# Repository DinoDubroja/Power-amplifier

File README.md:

# Power-amplifier
A general purpose power amplifier for lab use.

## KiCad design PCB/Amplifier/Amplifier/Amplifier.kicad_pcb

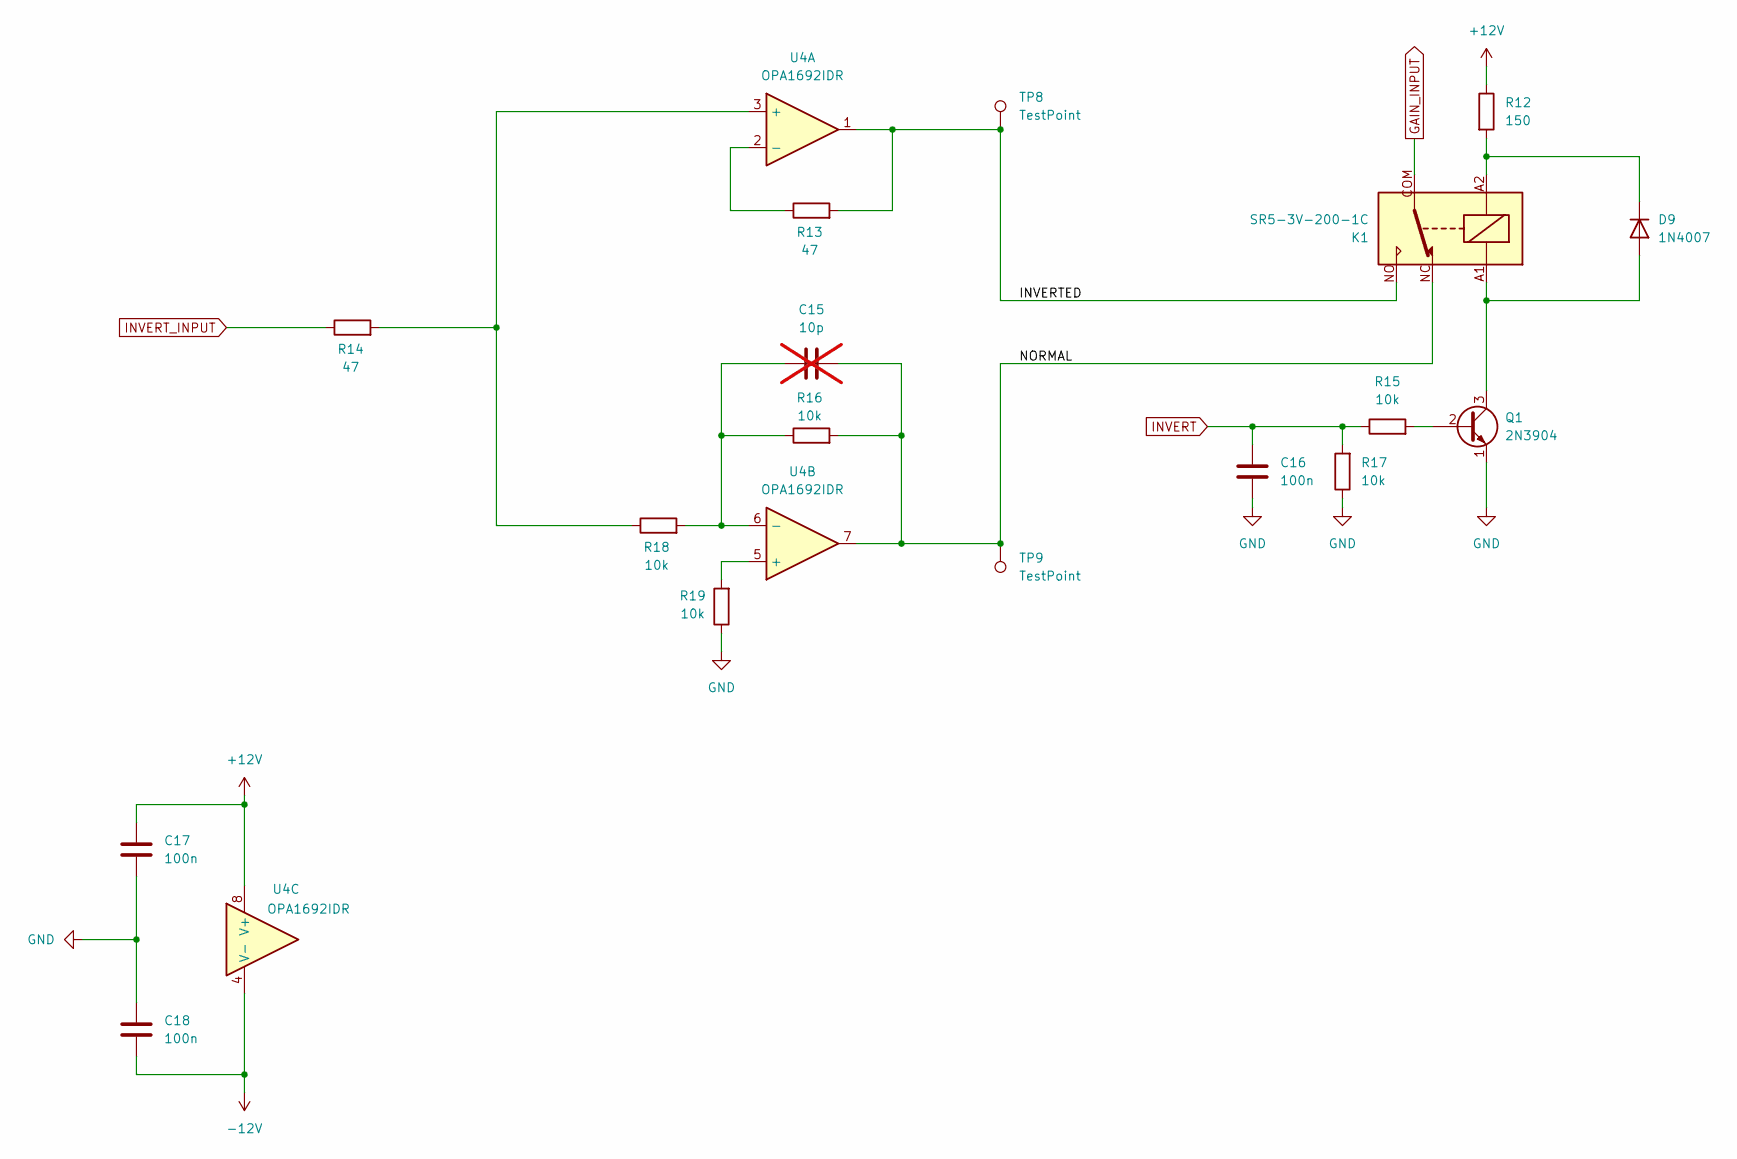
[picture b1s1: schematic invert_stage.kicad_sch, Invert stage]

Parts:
C15: 10p; C_Disc_D4.3mm_W1.9mm_P5.00mm; not fitted
C16, C17, C18: 100n; C_Disc_D4.3mm_W1.9mm_P5.00mm
D9: 1N4007; D_DO-15_P10.16mm_Horizontal
K1: SR5-3V-200-1C; SR53V2001C; Manufacturer_Part_Number SR5-3V-200-1C; Mouser Part Number 179-SR5-3V-200-1C
Q1: 2N3904; TO-92_Inline
R12: 150; R_Axial_DIN0207_L6.3mm_D2.5mm_P10.16mm_Horizontal
R13, R14: 47; R_Axial_DIN0207_L6.3mm_D2.5mm_P10.16mm_Horizontal
R15, R16, R17, R18, R19: 10k; R_Axial_DIN0207_L6.3mm_D2.5mm_P10.16mm_Horizontal
TP8, TP9: TestPoint; Pin_D1.2mm_L11.3mm_W3.0mm_Flat
U4: OPA1692IDR; SOIC127P600X175-8N; Manufacturer_Part_Number OPA1692IDR; Mouser Part Number 595-OPA1692IDR

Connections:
+12V: C17.1, R12.1, U4.8 (V+); also elsewhere on the board
-12V: C18.2, U4.4 (V-); also elsewhere on the board
/Invert stage/INVERTED: K1.NO, R13.2, TP8.1, U4.1
/Invert stage/NORMAL: C15.2, K1.NC, R16.2, TP9.1, U4.7
GAIN_INPUT: K1.COM; also elsewhere on the board
GND: C16.2, C17.2, C18.1, Q1.1 (E), R17.1, R19.1; also elsewhere on the board
INVERT: C16.1, R15.1, R17.2; also elsewhere on the board
INVERT_INPUT: R14.1; also elsewhere on the board
unnamed: D9.2 (A), K1.A1, Q1.3 (C)
unnamed: D9.1 (K), K1.A2, R12.2
unnamed: Q1.2 (B), R15.2
unnamed: R14.2, R18.1, U4.3 (+)
unnamed: R13.1, U4.2 (-)
unnamed: R19.2, U4.5 (+)
unnamed: C15.1, R16.1, R18.2, U4.6 (-)

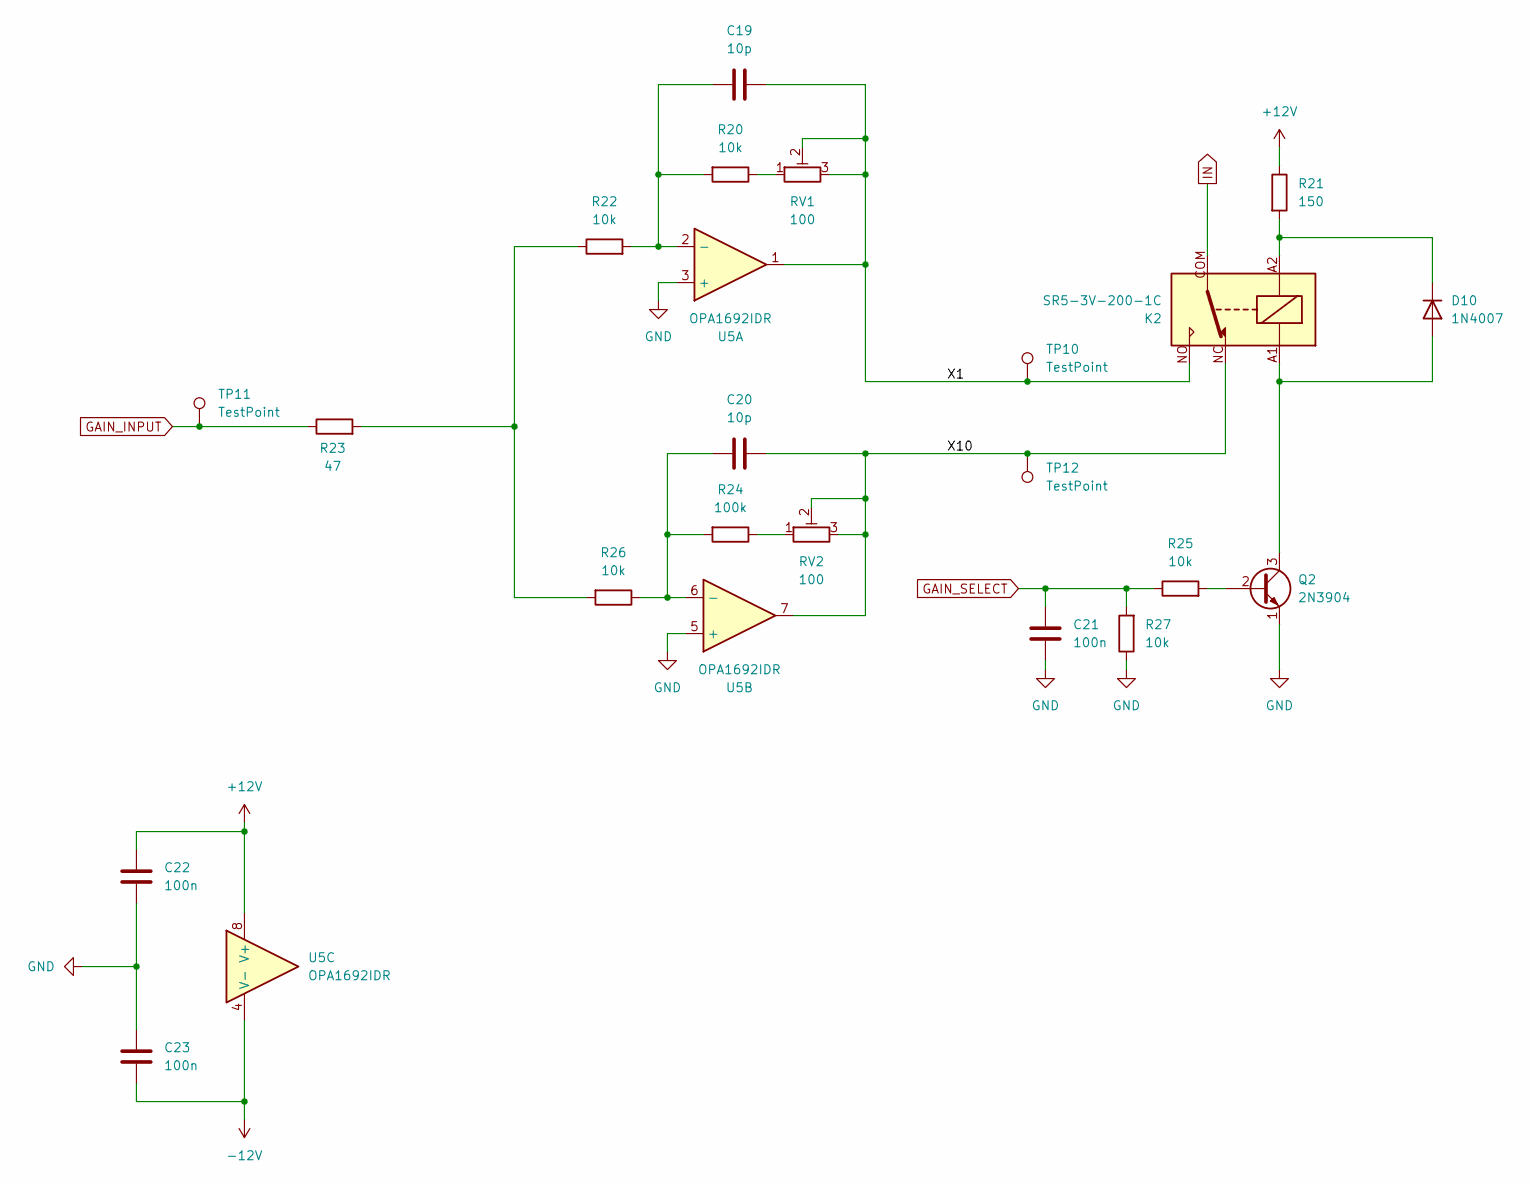
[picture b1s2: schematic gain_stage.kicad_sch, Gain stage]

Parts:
C19, C20: 10p; C_Disc_D4.3mm_W1.9mm_P5.00mm
C21, C22, C23: 100n; C_Disc_D4.3mm_W1.9mm_P5.00mm
D10: 1N4007; D_DO-15_P10.16mm_Horizontal
K2: SR5-3V-200-1C; SR53V2001C; Manufacturer_Part_Number SR5-3V-200-1C; Mouser Part Number 179-SR5-3V-200-1C
Q2: 2N3904; TO-92_Inline
R20, R22, R25, R26, R27: 10k; R_Axial_DIN0207_L6.3mm_D2.5mm_P10.16mm_Horizontal
R21: 150; R_Axial_DIN0207_L6.3mm_D2.5mm_P10.16mm_Horizontal
R23: 47; R_Axial_DIN0207_L6.3mm_D2.5mm_P10.16mm_Horizontal
R24: 100k; R_Axial_DIN0207_L6.3mm_D2.5mm_P10.16mm_Horizontal
RV1, RV2: 100; Potentiometer_Bourns_3296W_Vertical
TP10, TP11, TP12: TestPoint; Pin_D1.2mm_L11.3mm_W3.0mm_Flat
U5: OPA1692IDR; SOIC127P600X175-8N; Manufacturer_Part_Number OPA1692IDR; Mouser Part Number 595-OPA1692IDR

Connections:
+12V: C22.1, R21.1, U5.8 (V+); also elsewhere on the board
-12V: C23.2, U5.4 (V-); also elsewhere on the board
/Gain stage/X1: C19.2, K2.NO, RV1.2, RV1.3, TP10.1, U5.1
/Gain stage/X10: C20.2, K2.NC, RV2.2, RV2.3, TP12.1, U5.7
GAIN_INPUT: R23.1, TP11.1; also elsewhere on the board
GAIN_SELECT: C21.1, R25.1, R27.2; also elsewhere on the board
GND: C21.2, C22.2, C23.1, Q2.1 (E), R27.1, U5.3 (+), U5.5 (+); also elsewhere on the board
IN: K2.COM; also elsewhere on the board
unnamed: D10.2 (A), K2.A1, Q2.3 (C)
unnamed: D10.1 (K), K2.A2, R21.2
unnamed: Q2.2 (B), R25.2
unnamed: R20.1, RV1.1
unnamed: R22.1, R23.2, R26.2
unnamed: R24.1, RV2.1
unnamed: C19.1, R20.2, R22.2, U5.2 (-)
unnamed: C20.1, R24.2, R26.1, U5.6 (-)

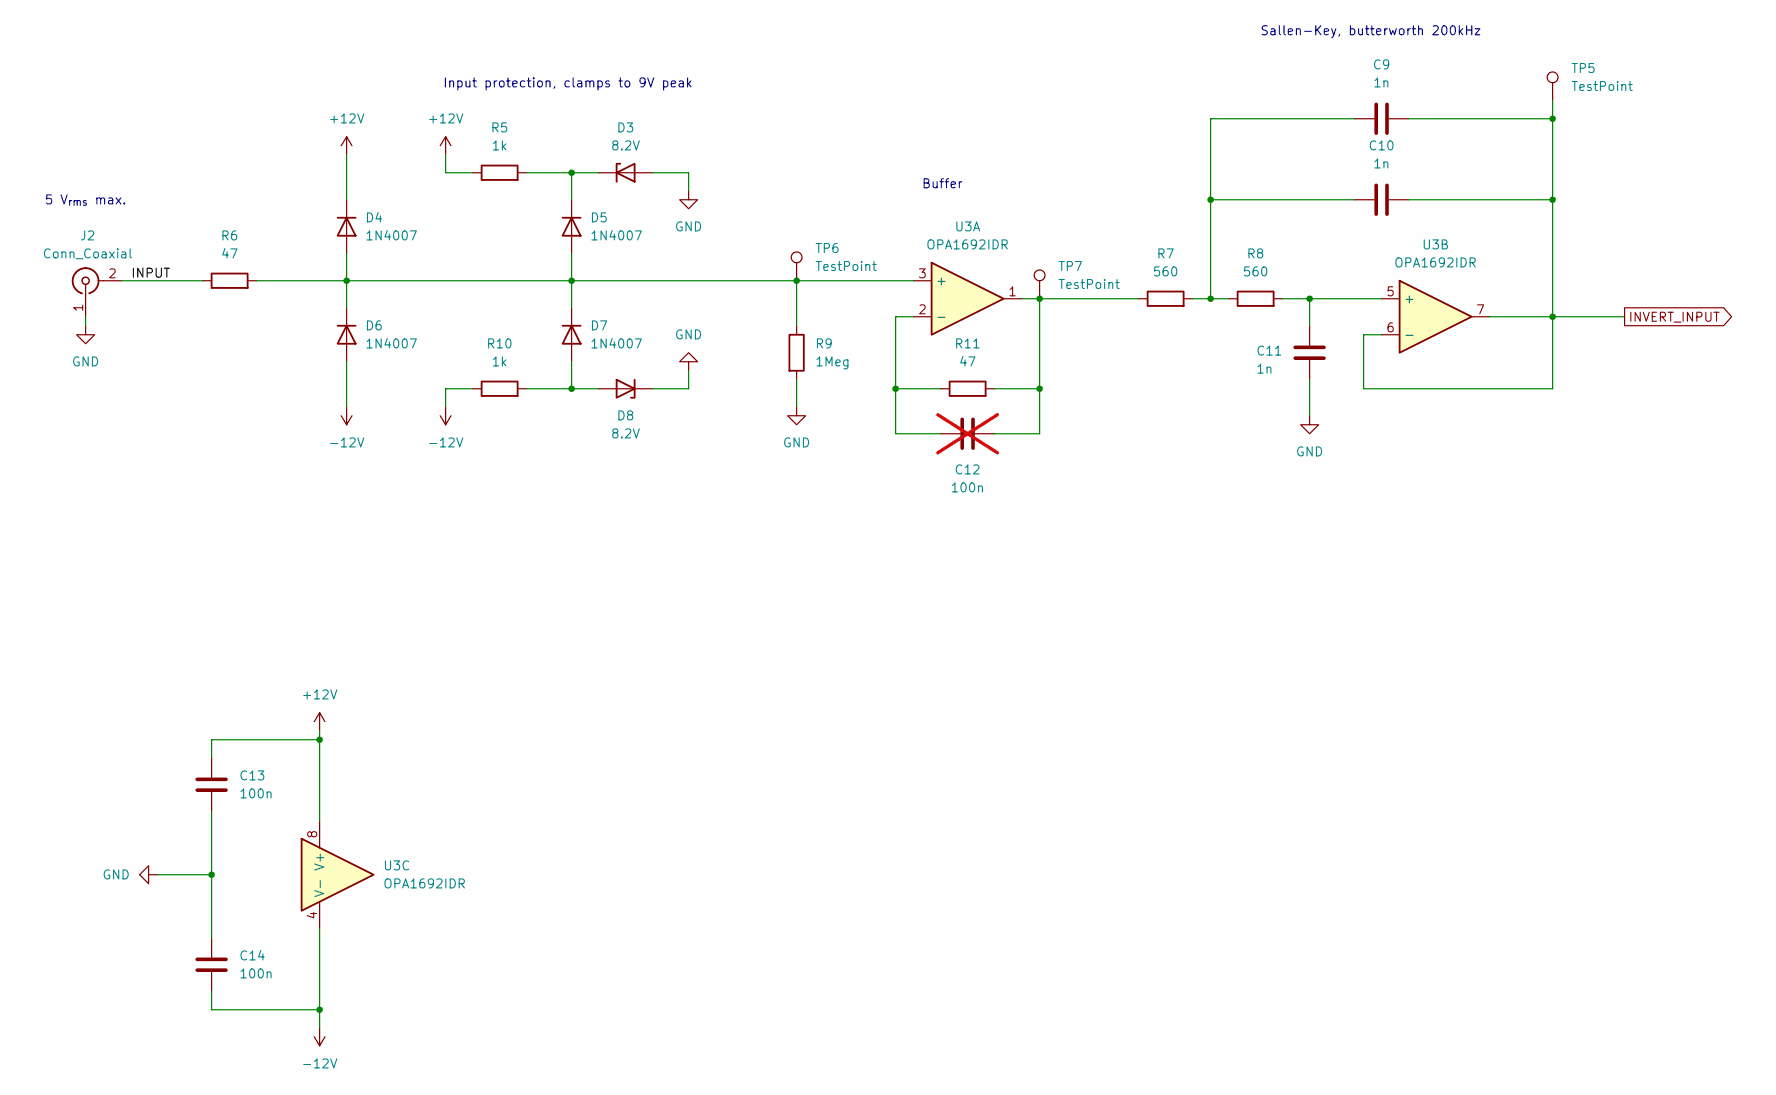
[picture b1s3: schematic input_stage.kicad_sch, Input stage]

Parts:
C9, C10, C11: 1n; C_Rect_L7.2mm_W2.5mm_P5.00mm_FKS2_FKP2_MKS2_MKP2
C12: 100n; C_Disc_D4.3mm_W1.9mm_P5.00mm; not fitted
C13, C14: 100n; C_Disc_D4.3mm_W1.9mm_P5.00mm
D3, D8: 8.2V; D_DO-35_SOD27_P10.16mm_Horizontal
D4, D5, D6, D7: 1N4007; D_DO-15_P10.16mm_Horizontal
J2: Conn_Coaxial; 52220061
R5, R10: 1k; R_Axial_DIN0207_L6.3mm_D2.5mm_P10.16mm_Horizontal
R6, R11: 47; R_Axial_DIN0207_L6.3mm_D2.5mm_P10.16mm_Horizontal
R7, R8: 560; R_Axial_DIN0207_L6.3mm_D2.5mm_P10.16mm_Horizontal
R9: 1Meg; R_Axial_DIN0207_L6.3mm_D2.5mm_P10.16mm_Horizontal
TP5, TP6, TP7: TestPoint; Pin_D1.2mm_L11.3mm_W3.0mm_Flat
U3: OPA1692IDR; SOIC127P600X175-8N; Manufacturer_Part_Number OPA1692IDR; Mouser Part Number 595-OPA1692IDR

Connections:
+12V: C13.1, D4.1 (K), R5.1, U3.8 (V+); also elsewhere on the board
-12V: C14.2, D6.2 (A), R10.1, U3.4 (V-); also elsewhere on the board
/Input stage/INPUT: J2.2 (Ext), R6.1
GND: C11.2, C13.2, C14.1, D3.2 (A), D8.1 (K), J2.1 (In), R9.2; also elsewhere on the board
INVERT_INPUT: C9.2, C10.2, TP5.1, U3.6 (-), U3.7; also elsewhere on the board
unnamed: C9.1, C10.1, R7.2, R8.1
unnamed: C12.2, R7.1, R11.2, TP7.1, U3.1
unnamed: D3.1 (K), D5.1 (K), R5.2
unnamed: D4.2 (A), D5.2 (A), D6.1 (K), D7.1 (K), R6.2, R9.1, TP6.1, U3.3 (+)
unnamed: D7.2 (A), D8.2 (A), R10.2
unnamed: C12.1, R11.1, U3.2 (-)
unnamed: C11.1, R8.2, U3.5 (+)

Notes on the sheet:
Input protection, clamps to 9V peak
5 V_{rms} max.
Buffer
Sallen-Key, butterworth 200kHz

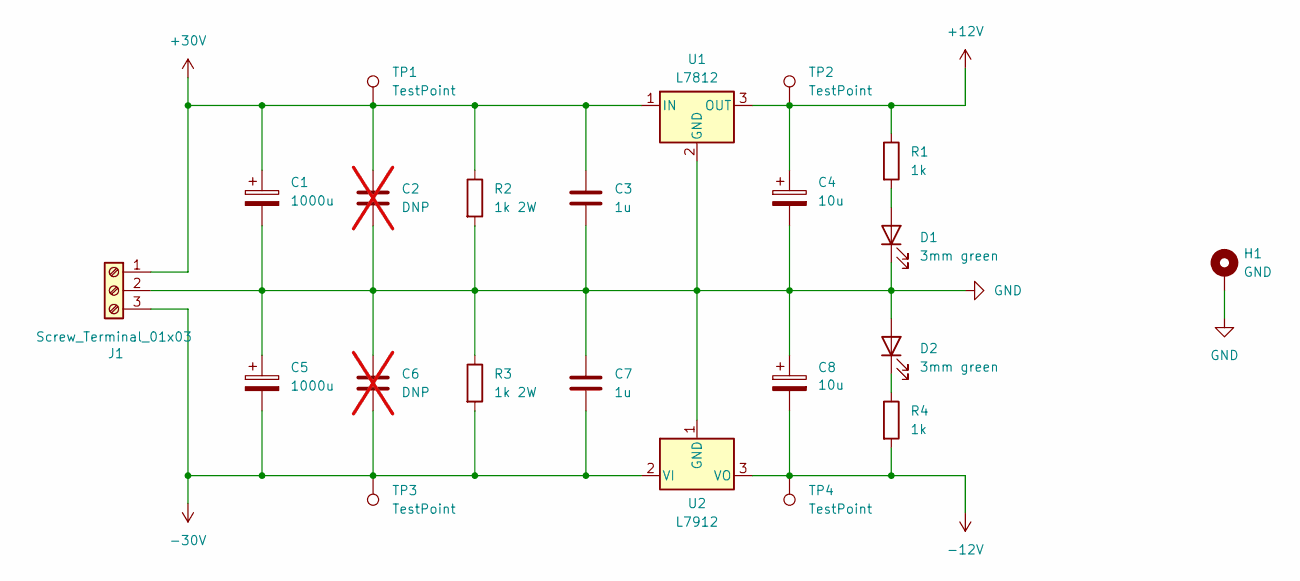
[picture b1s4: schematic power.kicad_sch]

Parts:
C1, C5: 1000u; CP_Radial_D16.0mm_P7.50mm
C2, C6: DNP; C_Disc_D4.3mm_W1.9mm_P5.00mm; not fitted
C3, C7: 1u; C_Rect_L7.2mm_W4.5mm_P5.00mm_FKS2_FKP2_MKS2_MKP2
C4, C8: 10u; CP_Radial_D4.0mm_P2.00mm
D1, D2: 3mm green; LED_D3.0mm
H1: GND; MountingHole_4.3mm_M4_Pad
J1: Screw_Terminal_01x03; TerminalBlock_Phoenix_MKDS-1,5-3_1x03_P5.00mm_Horizontal
R1, R4: 1k; R_Axial_DIN0207_L6.3mm_D2.5mm_P10.16mm_Horizontal
R2, R3: 1k 2W; R_Axial_DIN0411_L9.9mm_D3.6mm_P15.24mm_Horizontal
TP1, TP2, TP3, TP4: TestPoint; Pin_D1.2mm_L11.3mm_W3.0mm_Flat
U1: L7812; TO-220-3_Vertical
U2: L7912; TO-220-3_Vertical

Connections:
+12V: C4.1, R1.1, TP2.1, U1.3 (OUT); also elsewhere on the board
+30V: C1.1, C2.1, C3.1, J1.1, R2.1, TP1.1, U1.1 (IN); also elsewhere on the board
-12V: C8.2, R4.2, TP4.1, U2.3 (VO); also elsewhere on the board
-30V: C5.2, C6.2, C7.2, J1.3, R3.2, TP3.1, U2.2 (VI); also elsewhere on the board
GND: C1.2, C2.2, C3.2, C4.2, C5.1, C6.1, C7.1, C8.1, D1.1 (K), D2.2 (A), H1.1, J1.2, R2.2, R3.1, U1.2 (GND), U2.1 (GND); also elsewhere on the board
unnamed: D1.2 (A), R1.2
unnamed: D2.1 (K), R4.1

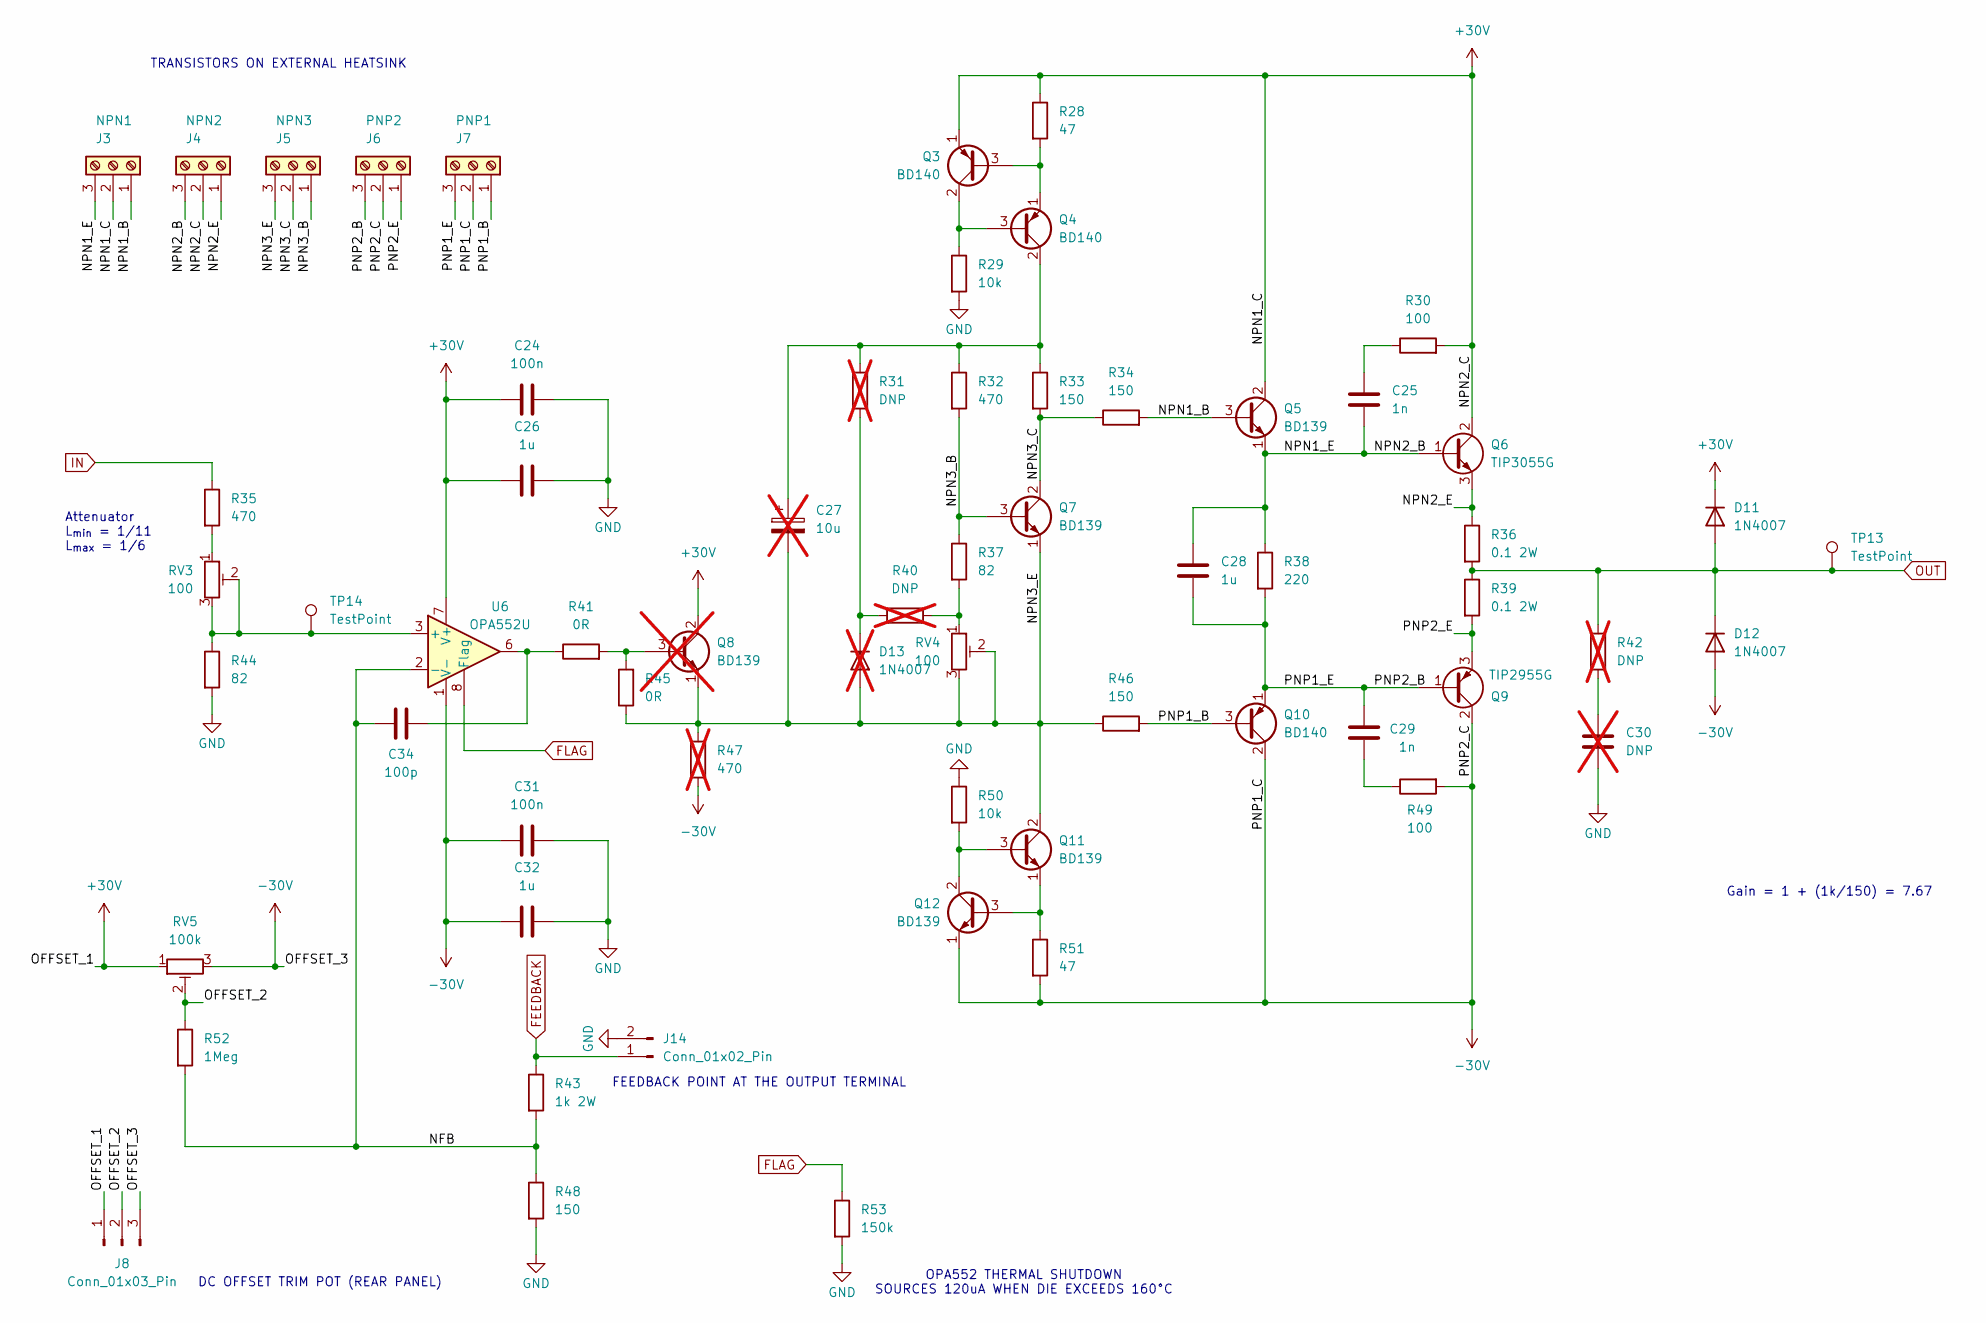
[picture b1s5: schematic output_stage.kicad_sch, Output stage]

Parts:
C24, C31: 100n; C_Disc_D4.3mm_W1.9mm_P5.00mm
C25, C29: 1n; C_Rect_L7.2mm_W2.5mm_P5.00mm_FKS2_FKP2_MKS2_MKP2
C26, C28, C32: 1u; C_Rect_L7.2mm_W4.5mm_P5.00mm_FKS2_FKP2_MKS2_MKP2
C27: 10u; CP_Radial_D4.0mm_P2.00mm; not fitted
C30: DNP; C_Disc_D4.3mm_W1.9mm_P5.00mm; not fitted
C34: 100p; C_Disc_D4.3mm_W1.9mm_P5.00mm
D11, D12: 1N4007; D_DO-15_P10.16mm_Horizontal
D13: 1N4007; D_DO-15_P10.16mm_Horizontal; not fitted
J3: NPN1; TerminalBlock_Phoenix_MKDS-1,5-3_1x03_P5.00mm_Horizontal
J4: NPN2; TerminalBlock_Phoenix_MKDS-1,5-3_1x03_P5.00mm_Horizontal
J5: NPN3; TerminalBlock_Phoenix_MKDS-1,5-3_1x03_P5.00mm_Horizontal
J6: PNP2; TerminalBlock_Phoenix_MKDS-1,5-3_1x03_P5.00mm_Horizontal
J7: PNP1; TerminalBlock_Phoenix_MKDS-1,5-3_1x03_P5.00mm_Horizontal
J8: Conn_01x03_Pin; JST_XH_B3B-XH-A_1x03_P2.50mm_Vertical
J14: Conn_01x02_Pin; JST_XH_B2B-XH-A_1x02_P2.50mm_Vertical
Q3, Q4: BD140; TO-126-3_Vertical
Q5, Q7: BD139; TerminalBlock_Phoenix_MKDS-1,5-3_1x03_P5.00mm_Horizontal
Q6: TIP3055G; TerminalBlock_Phoenix_MKDS-1,5-3_1x03_P5.00mm_Horizontal
Q8: BD139; TO-126-3_Vertical; not fitted
Q9: TIP2955G; TerminalBlock_Phoenix_MKDS-1,5-3_1x03_P5.00mm_Horizontal
Q10: BD140; TerminalBlock_Phoenix_MKDS-1,5-3_1x03_P5.00mm_Horizontal
Q11, Q12: BD139; TO-126-3_Vertical
R28, R51: 47; R_Axial_DIN0207_L6.3mm_D2.5mm_P10.16mm_Horizontal
R29, R50: 10k; R_Axial_DIN0207_L6.3mm_D2.5mm_P10.16mm_Horizontal
R30, R49: 100; R_Axial_DIN0207_L6.3mm_D2.5mm_P10.16mm_Horizontal
R31, R40, R42: DNP; R_Axial_DIN0207_L6.3mm_D2.5mm_P10.16mm_Horizontal; not fitted
R32, R35: 470; R_Axial_DIN0207_L6.3mm_D2.5mm_P10.16mm_Horizontal
R33, R34, R46, R48: 150; R_Axial_DIN0207_L6.3mm_D2.5mm_P10.16mm_Horizontal
R36, R39: 0.1 2W; R_Axial_DIN0516_L15.5mm_D5.0mm_P20.32mm_Horizontal
R37, R44: 82; R_Axial_DIN0207_L6.3mm_D2.5mm_P10.16mm_Horizontal
R38: 220; R_Axial_DIN0207_L6.3mm_D2.5mm_P10.16mm_Horizontal
R41, R45: 0R; R_Axial_DIN0207_L6.3mm_D2.5mm_P10.16mm_Horizontal
R43: 1k 2W; R_Axial_DIN0411_L9.9mm_D3.6mm_P15.24mm_Horizontal
R47: 470; R_Axial_DIN0207_L6.3mm_D2.5mm_P10.16mm_Horizontal; not fitted
R52: 1Meg; R_Axial_DIN0207_L6.3mm_D2.5mm_P10.16mm_Horizontal
R53: 150k; R_Axial_DIN0207_L6.3mm_D2.5mm_P10.16mm_Horizontal
RV3, RV4: 100; Potentiometer_Bourns_3296W_Vertical
RV5: 100k
TP13, TP14: TestPoint; Pin_D1.2mm_L11.3mm_W3.0mm_Flat
U6: OPA552U; SOIC-8_3.9x4.9mm_P1.27mm

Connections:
+30V: C24.1, C26.1, D11.1 (K), J3.2, J4.2, J8.1, Q3.1 (E), Q5.2 (C), Q6.2 (C), Q8.2 (C), R28.1, R30.2, RV5.1, U6.7 (V+); also elsewhere on the board
-30V: C31.1, C32.1, D12.2 (A), J6.2, J7.2, J8.3, Q9.2 (C), Q10.2 (C), Q12.1 (E), R47.1, R49.2, R51.2, RV5.3, U6.1 (V-), U6.4 (V-), U6.5 (V-); also elsewhere on the board
/Output stage/NFB: C34.1, R43.2, R48.1, R52.2, U6.2 (-)
/Output stage/NPN1_B: J3.1, Q5.3 (B), R34.2
/Output stage/NPN1_E: C25.2, C28.1, J3.3, J4.3, Q5.1 (E), Q6.1 (B), R38.1
/Output stage/NPN2_E: J4.1, Q6.3 (E), R36.1
/Output stage/NPN3_B: J5.1, Q7.3 (B), R32.2, R37.1
/Output stage/NPN3_C: J5.2, Q7.2 (C), R33.2, R34.1
/Output stage/NPN3_E: C27.2, D13.2 (A), J5.3, Q7.1 (E), Q8.1 (E), Q11.2 (C), R45.1, R46.1, R47.2, RV4.2, RV4.3
/Output stage/OFFSET_2: J8.2, R52.1, RV5.2
/Output stage/PNP1_B: J7.1, Q10.3 (B), R46.2
/Output stage/PNP1_E: C28.2, C29.2, J6.3, J7.3, Q9.1 (B), Q10.1 (E), R38.2
/Output stage/PNP2_E: J6.1, Q9.3 (E), R39.2
FEEDBACK: J14.1, R43.1
FLAG: R53.1, U6.8 (Flag); also elsewhere on the board
GND: C24.2, C26.2, C30.2, C31.2, C32.2, J14.2, R29.2, R44.2, R48.2, R50.1, R53.2; also elsewhere on the board
IN: R35.1; also elsewhere on the board
unnamed: C25.1, R30.1
unnamed: C29.1, R49.1
unnamed: C30.1, R42.2
unnamed: C34.2, R41.1, U6.6
unnamed: D13.1 (K), R31.1, R40.2
unnamed: Q3.3 (B), Q4.1 (E), R28.2
unnamed: Q3.2 (C), Q4.3 (B), R29.1
unnamed: C27.1, Q4.2 (C), R31.2, R32.1, R33.1
unnamed: Q8.3 (B), R41.2, R45.2
unnamed: Q11.3 (B), Q12.2 (C), R50.2
unnamed: Q11.1 (E), Q12.3 (B), R51.1
unnamed: R35.2, RV3.1
unnamed: R37.2, R40.1, RV4.1
unnamed: R44.1, RV3.2, RV3.3, TP14.1, U6.3 (+)
OUT: D11.2 (A), D12.1 (K), R36.2, R39.1, R42.1, TP13.1; also elsewhere on the board

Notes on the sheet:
FEEDBACK POINT AT THE OUTPUT TERMINAL
OPA552 THERMAL SHUTDOWN SOURCES 120uA WHEN DIE EXCEEDS 160°C
DC OFFSET TRIM POT (REAR PANEL)
Gain = 1 + (1k/150) = 7.67
TRANSISTORS ON EXTERNAL HEATSINK
Attenuator L_{min} = 1/11 L_{max} = 1/6

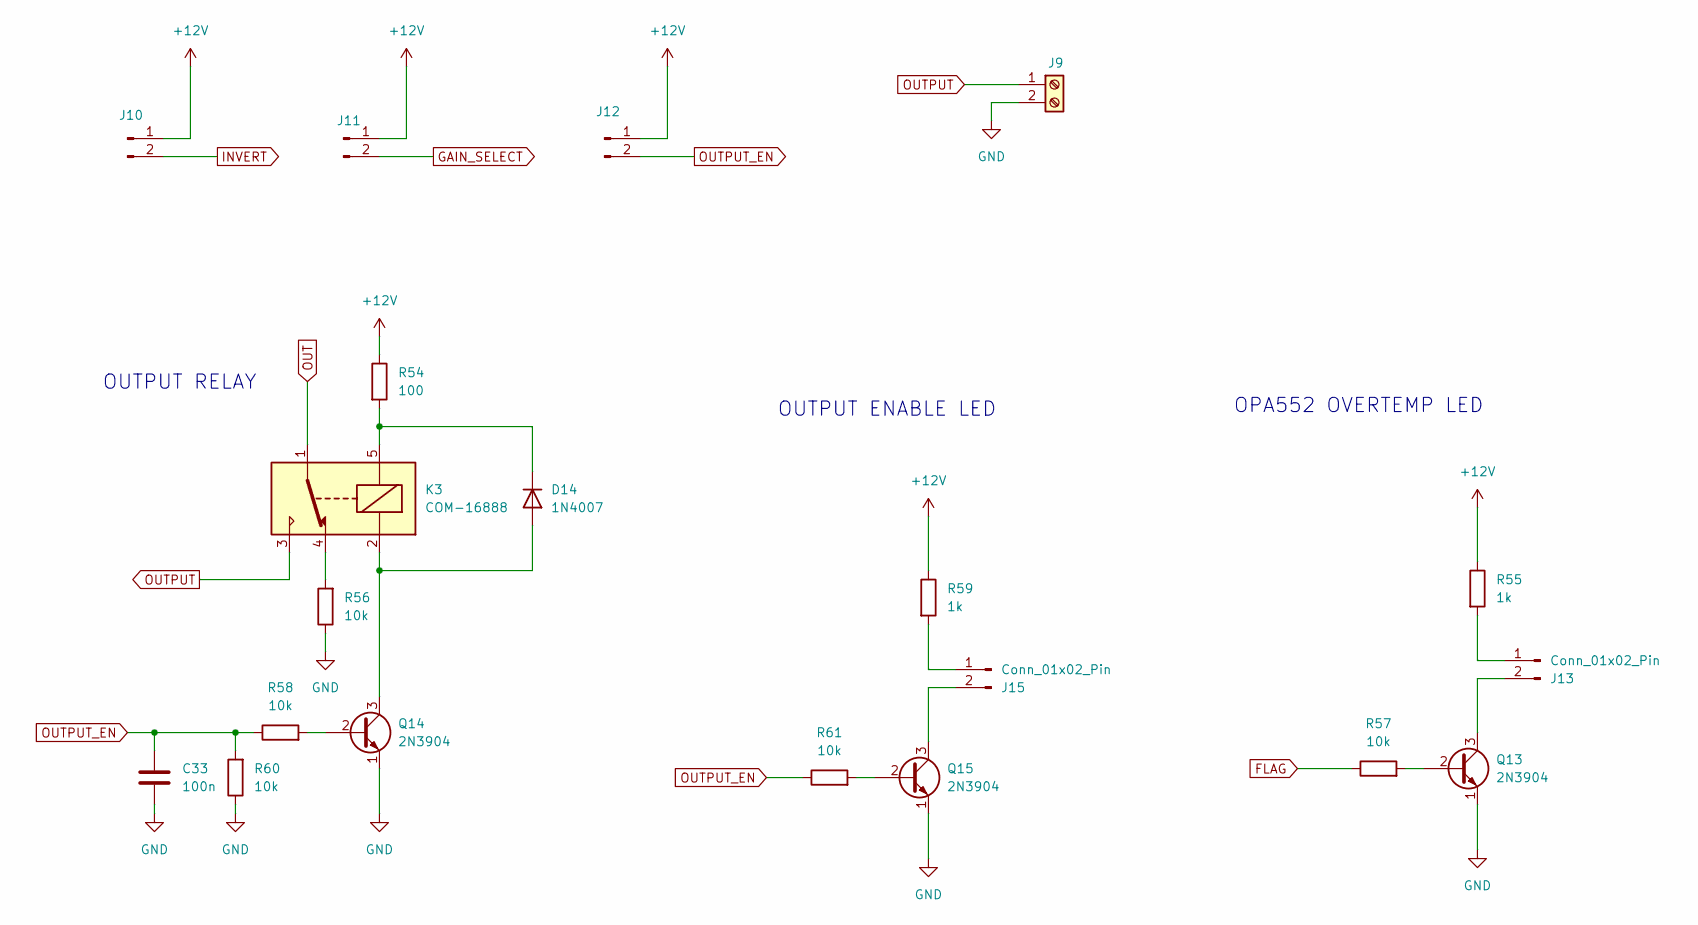
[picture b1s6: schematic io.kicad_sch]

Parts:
C33: 100n; C_Disc_D4.3mm_W1.9mm_P5.00mm
D14: 1N4007; D_DO-15_P10.16mm_Horizontal
J9: Screw_Terminal_01x02; TerminalBlock_Phoenix_MKDS-1,5-2-5.08_1x02_P5.08mm_Horizont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
J10, J11, J12, J13, J15: Conn_01x02_Pin; JST_XH_B2B-XH-A_1x02_P2.50mm_Vertical
K3: COM-16888; COM16888; Mouser Part Number 474-COM-16888
Q13, Q14, Q15: 2N3904; TO-92_Inline
R54: 100; R_Axial_DIN0207_L6.3mm_D2.5mm_P10.16mm_Horizontal
R55, R59: 1k; R_Axial_DIN0207_L6.3mm_D2.5mm_P10.16mm_Horizontal
R56, R57, R58, R60, R61: 10k; R_Axial_DIN0207_L6.3mm_D2.5mm_P10.16mm_Horizontal

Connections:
+12V: J10.1, J11.1, J12.1, R54.1, R55.1, R59.1; also elsewhere on the board
FLAG: R57.1; also elsewhere on the board
GAIN_SELECT: J11.2; also elsewhere on the board
GND: C33.2, J9.2, Q13.1 (E), Q14.1 (E), Q15.1 (E), R56.1, R60.1; also elsewhere on the board
INVERT: J10.2; also elsewhere on the board
unnamed: D14.2 (A), K3.2 (COIL_1), Q14.3 (C)
unnamed: D14.1 (K), K3.5 (COIL_2), R54.2
unnamed: J13.1, R55.2
unnamed: J13.2, Q13.3 (C)
unnamed: J15.1, R59.2
unnamed: J15.2, Q15.3 (C)
unnamed: K3.4 (NC), R56.2
unnamed: Q13.2 (B), R57.2
unnamed: Q14.2 (B), R58.2
unnamed: Q15.2 (B), R61.2
OUT: K3.1 (COM); also elsewhere on the board
OUTPUT: J9.1, K3.3 (NO)
OUTPUT_EN: C33.1, J12.2, R58.1, R60.2, R61.1

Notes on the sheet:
OPA552 OVERTEMP LED
OUTPUT RELAY
OUTPUT ENABLE LED

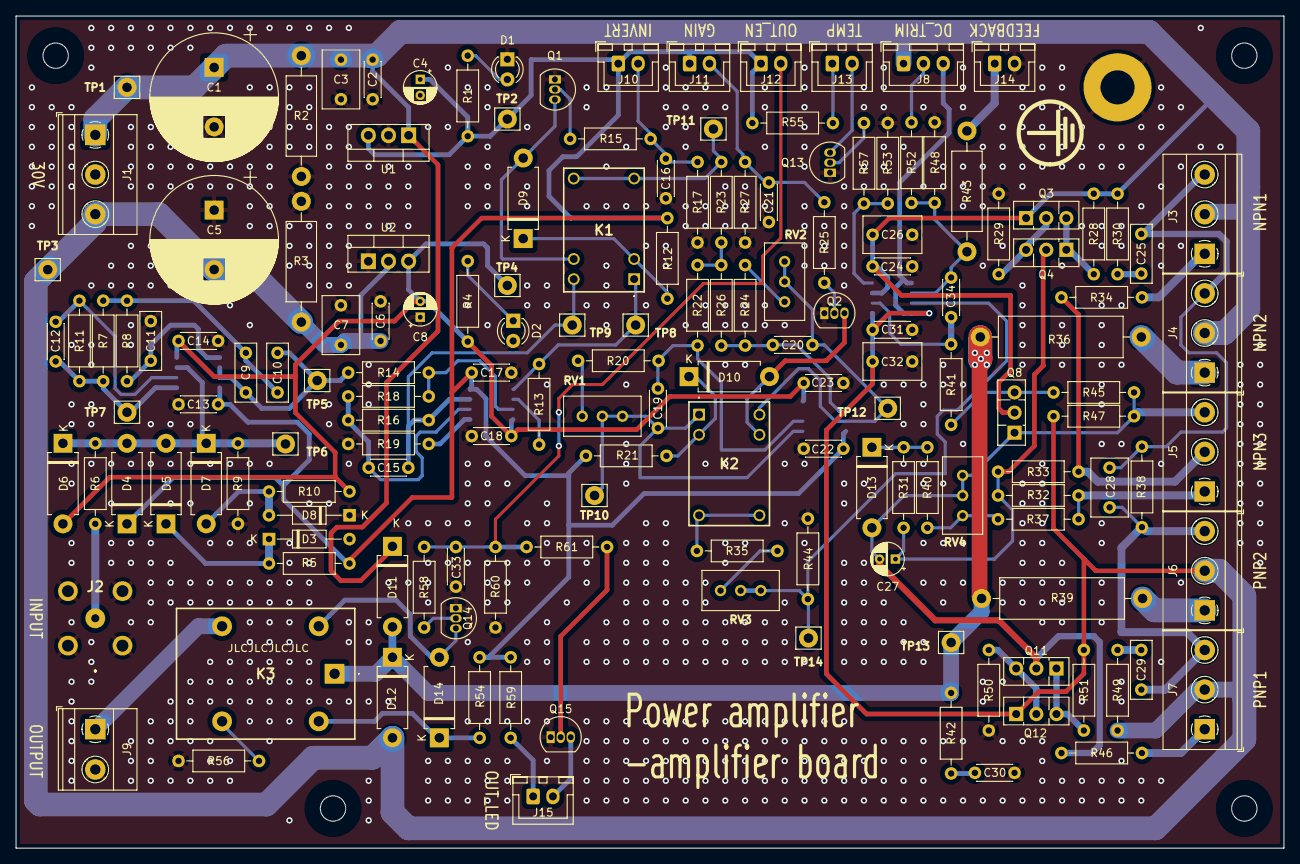
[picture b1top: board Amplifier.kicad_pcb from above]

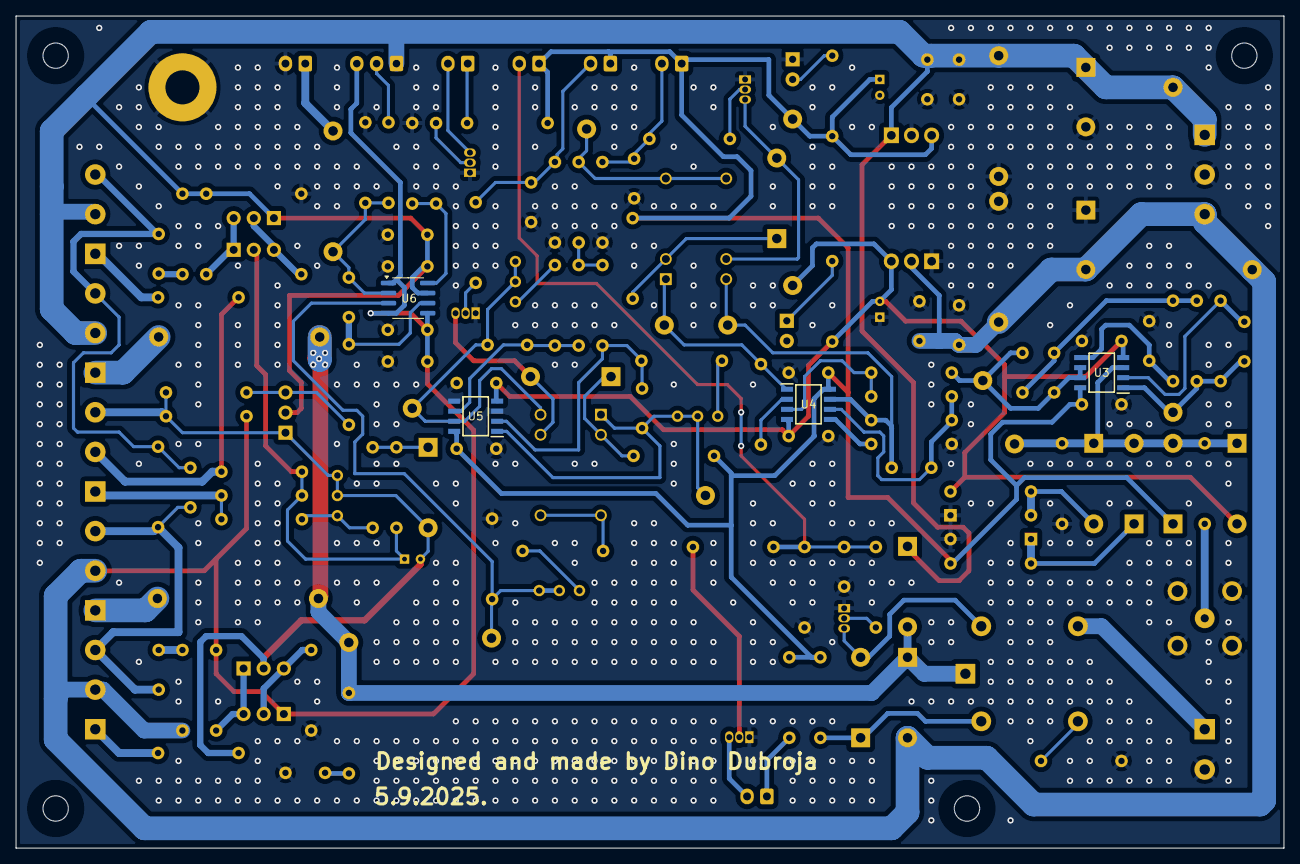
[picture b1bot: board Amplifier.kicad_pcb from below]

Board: 2 copper layers, 160.0 x 105.0 mm, 162 parts (4 on the bottom side), 79 nets.

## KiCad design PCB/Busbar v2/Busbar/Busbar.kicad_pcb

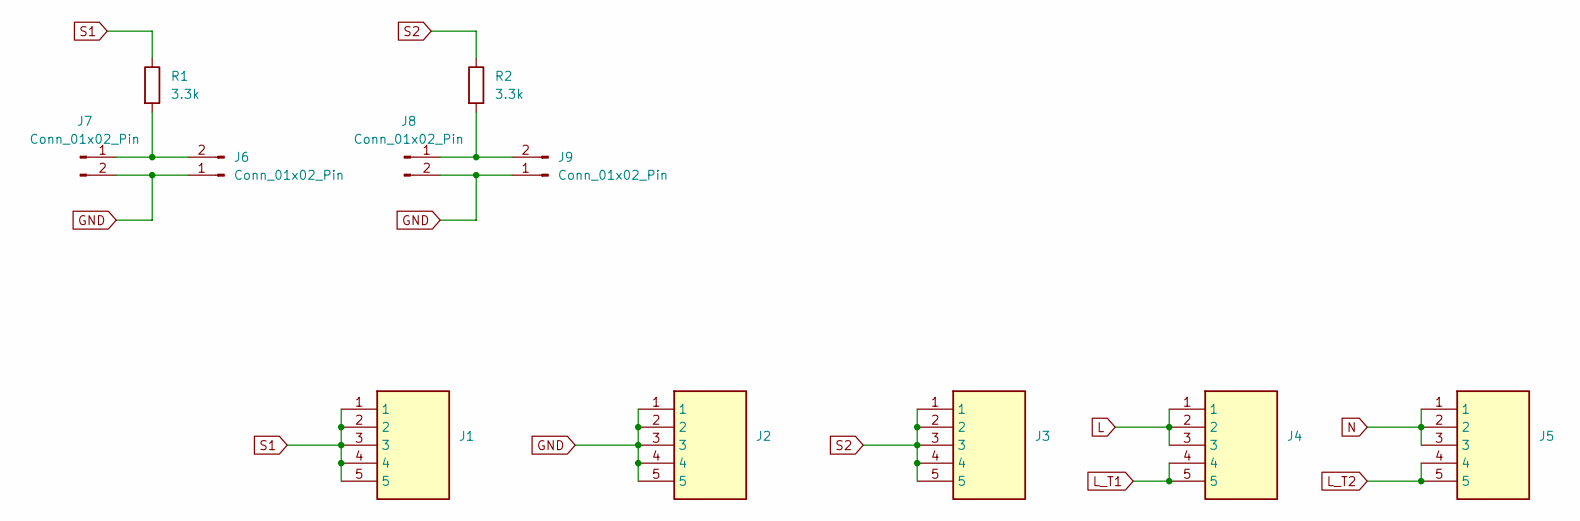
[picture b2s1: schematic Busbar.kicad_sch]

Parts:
J1, J2, J3, J4, J5: 4DB-P108-05; 4DBP10805; Mouser Part Number 571-214376678
J6, J7, J8, J9: Conn_01x02_Pin; JST_XH_S2B-XH-A-1_1x02_P2.50mm_Horizontal
R1, R2: 3.3k; R_Axial_DIN0207_L6.3mm_D2.5mm_P10.16mm_Horizontal

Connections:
GND: J2.1, J2.2, J2.3, J2.4, J2.5, J6.1, J7.2, J8.2, J9.1
L: J4.1, J4.2, J4.3
L_T1: J4.4, J4.5
L_T2: J5.4, J5.5
N: J5.1, J5.2, J5.3
unnamed: J6.2, J7.1, R1.2
unnamed: J8.1, J9.2, R2.2
S1: J1.1, J1.2, J1.3, J1.4, J1.5, R1.1
S2: J3.1, J3.2, J3.3, J3.4, J3.5, R2.1

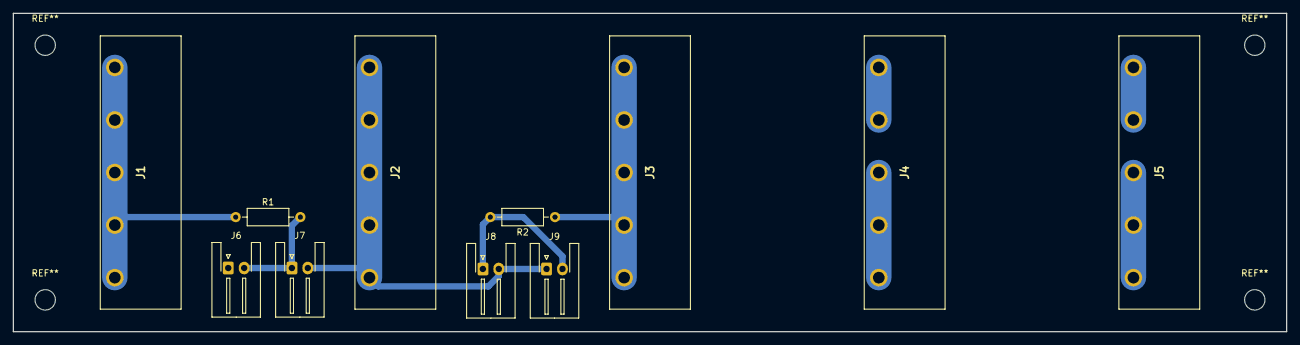
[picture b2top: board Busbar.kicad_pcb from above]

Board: 2 copper layers, 200.0 x 50.0 mm, 11 parts (0 on the bottom side), 9 nets.
